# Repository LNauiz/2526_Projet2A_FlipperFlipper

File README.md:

# 2526_Projet2A_Flipper
Notre objectif est de réaliser un Flipper (ou billard électrique). Notre flipper aurait tous les éléments suivants : les batteurs, les bumpers, un lanceur, un compteur de point et des éclairages (réalisés avec des néopixels), tels que montré sur les dessins suivants : 

Afin de marquer des points, le joueur doit soit passer entre les dauphins soit tapper contre les pièces triangulaires ou contre les bumpers.
### Matériel
* Solénoïdes*4 : Heschen Electroaimant solénoïde, HS-1546B, DC24V, 1.5A, course 20 mm, type Push Pull

* Néopixels alimentées à 5 V

* Photodiodes*3

* Détails de la PCB seront donnés dans la partie concernée

### Logiciels utilisés
KiCAD (design PCB), STM32CubeIDE (Software), Onshape (Modélisation 3D)

## Les Bumpers

Le fonctionnement du bumper est le suivant : lorsque la balle arrive contre le bumper, elle boucle un circuit entre un anneau proche du circuit ainsi que le cylindre central ce qui va provoquer l'abattement d'une collerette (nommée "metal flange with studs" sur le schéma) repoussant ainsi la balle.
Pour réaliser cet "abattement" on utilise des **solénoïdes** que nous commençons par tester : 
### _Premier test solénoïde_

Afin d'utiliser ces solénoïdes pour réaliser des bumpers nous avons besoin d'un support (que nous avons dessiné sur Onshape) :

Pour relier la colerette au solénoïde, on utilise des tiges filetés et des écrous nylstop ainsi qu'une pièce imprimé en 3d calée dans le solénoïde.

Afin de détecter si la balle a touché le bumper, nous avons entouré la base et le mât du bumper de scotch cuivré. La balle, en contact avec les deux morceaux de scotch, ferme le cicuit connecté à un GPIO pin de la STM, ce qui permet de commander le solénoïde du bumper.

## Les Batteurs
Les batteurs sont au nombre de 2 et seront contrôlés par des boutons poussoirs qui activeront d'autres solénoïdes. Ainsi nous avons du réaliser un dispositif afin de pouvoir tranformer la translation produite par le solénoïde en rotation de 60° pour les batteurs. Par Onshape, on modélise les pièces suivantes : 

Il est nécessaire d'ajouter des écrous nylstops à l'intérieur des pièces pour ne pas que ces derniers se dévissent.\
Malgré cela, on a remarqué que les écrous nylstops avaient une certaine marge de mouvement, ce qui désaxe les batteurs au fil du temps.

## Le Lanceur
La première idée afin de réaliser le lanceur est de réaliser un Coilgun dont le principe est le suivant : 
Nous prenons une balle de 25mm de diamètre que nous voulons faire aller à **6 m/s** lors du lancement ainsi le dimmensionnement de notre Coilgun serait le suivant : 

Nous avons fini par nous rabattre sur un simple ressort monté sur une tige filetée.

## Les boutons

Après plusieurs tests, nous avons remarqué que les boutons qui étaient, d'après la datasheet, pour du 5V fonctionnaient en 24V. Afin d'avoir un prototype "fonctionnel", nous avons donc simplement branché les batteurs de cette manière: 24V --- Bouton --- Batteur.\

## Le Compteur
Afin d'afficher le score réalisé par le joueur nous devons réaliser un compteur, on utilisera un afficheur 7 segments.\
Pour ce faire nous utiliserons des Néopixels, le code serait réalisé en langage C.\
Voici le support (réalisé sur Onshape) sur lequel nous voulons coller et souder les néopixels : 

Afin de dissiper la lumière pour ne pas être ébloui par les LED, on peut mettre un difuseur lumineux qui se compose de 1 à 2 couches de PLA.\
Nous avons remarqué que chaque LED doit être séparé par un mur afin de ne pas éclairer les parties des autres (par exemple: le 1 ressemble au 3 sans mur).

## Les Photodiodes
Afin de détecter lorsque la balle passe entre les obstacles ou lorsqu'elle heurte l'obstacle triangulaire du milieu de la table, nous utilisons des photodiodes.
Les premiers tests avec un PCB fait par Monsieur Papazoglou ont été laborieux, on remarque que pour vérifier que ces photodiodes sont bien fonctionnelles nous pouvons lorsqu'elles sont branchées utiliser l'appareil photo de notre téléphone, lorsqu'une lumière violette (le laser) émane de la photodiode, cette dernière est fonctionnelle, si ce n'est pas le cas cela signifie que la photodiode a subi une dégradation irréversible (sûrement du à une alimentation excessive).

## Le PCB
Afin de commander les solénoïdes nous avons réalisé (sur KiCAD) et soudé un premier PCB que voici : 

Lors des soudures nous avons rencontré plusieurs problèmes tels que des empreintes erronées (une résistance R et un condensateur sous-estimés en taille et une patte manquante sur les MOSFETs)
Lors des tests, le Buck de ce premier PCB est fortement monté en température. Nous sommes donc passé au montage suivant (PCB corrigé par Monsieur Papazoglou) :

Lors des test, le Buck de ce PCB est également monté en température. Nous pensons que le problème viendrait d'un court-circuit créé lors de la soudure Pour poursuivre notre projet nous pensons donc changer le buck qui nous cause problème quel que soit le montage par le même type de régulateur à 3 pin que ce celui qui transforme le 24V en 12V. Nous avons construit le PCB avec la possibilité de séparer la partie puissance et la partie commande. Nous avons donc prévu de tester cette dernière lors des prochaines semaines et de commencer à concevoir le PCB final qui commandera l'ensemble du système.

Le PCB final a été réalisé

## Software

Voici le schéma fonctionnel de notre système.

Il nous faut donc jeter un coup d'oeil aux différents capteurs afin de savoir quel information la STM va recevoir. 

## La table de jeux
Afin de réaliser la table de jeux de notre flipper, nous avons décidé de la faire en 2 couches pour y encastrer les différents modules (bumper, batteur...).
Notre première couche est du MDF de 3 mm, gravé afin que nous puissions placer les élèments de la table le mieux possible (rampe de lancement, dauphins...)

Notre deuxième couche est du MDF de 6 mm, des trous d'alignement sont prévus dans les 2 couches pour faciliter la construction

Voici le rendu final de la table, une fois assemblée (il faudrait coller les 2 couches de table pour avoir un meilleur rendu)

## Le Châssis
Afin d'avoir un support pour notre flipper, nous avons dessiné sur Onshape un châssis en prenant en compte la pente réglementaire pour un Flipper classique qui est de **6,5 °**.

Le châssis comporte une ouverture afin d'y brancher l'alimentation ainsi que des aérations permettant la ventilation de notre système.
Après avoir réalisé ceci nous sommes entrain de faire la table de jeux qui sera réalisé en 2 couches (afin de pouvoir varier les épaisseurs et de pouvoir y emboîter les supports pour bumper ou batteur)

# Licence
Licence : MIT

Auteurs : Julie Deissard--Decot, Léonard Navizet, Maxime Beltoise, Johann Mansard

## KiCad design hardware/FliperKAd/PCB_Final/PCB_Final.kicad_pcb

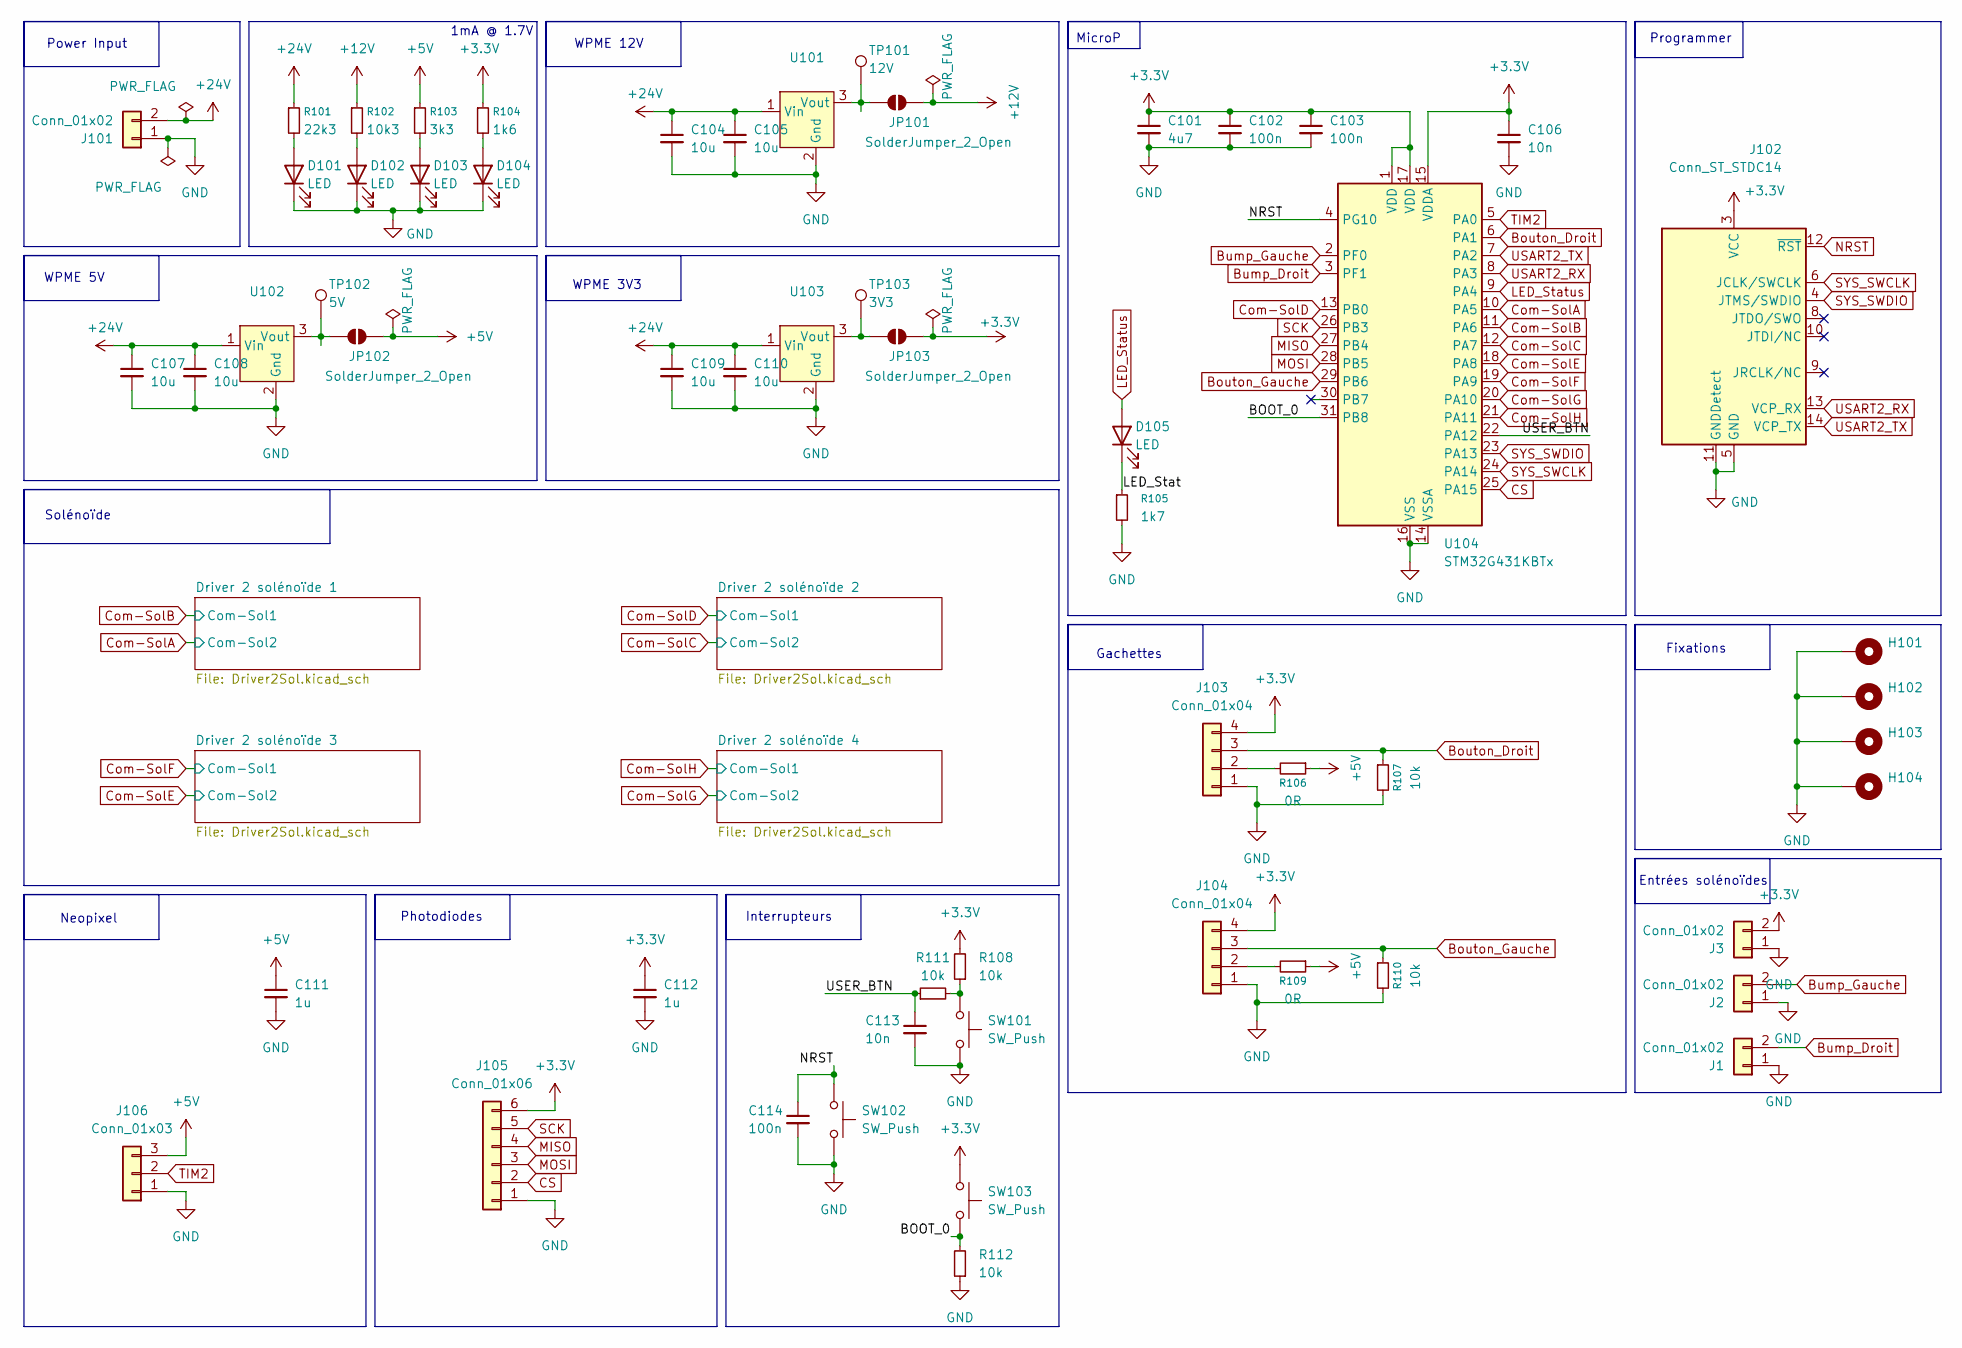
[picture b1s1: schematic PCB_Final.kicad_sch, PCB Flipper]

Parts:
C101: 4u7; C_0603_1608Metric
C102, C103, C114: 100n; C_0402_1005Metric
C104, C105, C107, C108, C109, C110: 10u; C_1206_3216Metric
C106, C113: 10n; C_0402_1005Metric
C111, C112: 1u; C_0603_1608Metric
D101: LED; LED_0603_1608Metric; MPN 150060RS55040
D102, D103, D104, D105: LED; LED_0603_1608Metric
H101, H102, H103, H104: MountingHole_Pad; MountingHole_3.2mm_M3_Pad_Via
J1, J2, J3: Conn_01x02; JST_PH_B2B-PH-K_1x02_P2.00mm_Vertical
J101: Conn_01x02; AMASS_XT30U-F_1x02_P5.0mm_Vertical
J102: Conn_ST_STDC14; PinHeader_2x07_P1.27mm_Vertical_SMD
J103, J104: Conn_01x04; JST_PH_B4B-PH-K_1x04_P2.00mm_Vertical
J105: Conn_01x06; JST_PH_B6B-PH-K_1x06_P2.00mm_Vertical
J106: Conn_01x03; JST_PH_B3B-PH-K_1x03_P2.00mm_Vertical
JP101, JP102, JP103: SolderJumper_2_Open; SolderJumper-2_P1.3mm_Open_TrianglePad1.0x1.5mm
R101: 22k3; R_0402_1005Metric
R102: 10k3; R_0402_1005Metric
R103: 3k3; R_0402_1005Metric
R104: 1k6; R_0402_1005Metric
R105: 1k7; R_0402_1005Metric
R106, R109: 0R; R_0402_1005Metric
R107, R108, R110, R111, R112: 10k; R_0402_1005Metric
SW101, SW102, SW103: SW_Push; SW_SPST_B3U-3000P; MPN KSS221GLFS
TP101: 12V; TestPoint_Pad_D2.0mm
TP102: 5V; TestPoint_Pad_D2.0mm
TP103: 3V3; TestPoint_Pad_D2.0mm
U101: 173951275; MPN 173951275
U102: 173951275; MPN 173950575
U103: 173951275; MPN 173950375
U104: STM32G431KBTx; LQFP-32_7x7mm_P0.8mm

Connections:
+3.3V: C101.1, C102.1, C103.1, C106.1, C112.1, J3.2, J102.3 (VCC), J103.4, J104.4, J105.6, JP103.2 (B), R104.1, R108.2, SW103.1, U104.1 (VDD), U104.15 (VDDA), U104.17 (VDD)
+5V: C111.1, J106.3, JP102.2 (B), R103.1, R106.1, R109.1
+12V: JP101.2 (B), R102.1; also elsewhere on the board
+24V: C104.1, C105.1, C107.1, C108.1, C109.1, C110.1, J101.2, R101.1, U101.1 (Vin), U102.1 (Vin), U103.1 (Vin); also elsewhere on the board
/BOOT_0: R112.2, SW103.2, U104.31 (PB8)
/LED_Stat: D105.1 (K), R105.1
/USER_BTN: C113.1, R111.1, U104.22 (PA12)
Bouton_Droit: J103.3, R107.1, U104.6 (PA1)
Bouton_Gauche: J104.3, R110.1, U104.29 (PB6)
Bump_Droit: J1.2, U104.3 (PF1)
Bump_Gauche: J2.2, U104.2 (PF0)
CS: J105.2, U104.25 (PA15)
Com-SolA: U104.10 (PA5); also elsewhere on the board
Com-SolB: U104.11 (PA6); also elsewhere on the board
Com-SolC: U104.12 (PA7); also elsewhere on the board
Com-SolD: U104.13 (PB0); also elsewhere on the board
Com-SolE: U104.18 (PA8); also elsewhere on the board
Com-SolF: U104.19 (PA9); also elsewhere on the board
Com-SolG: U104.20 (PA10); also elsewhere on the board
Com-SolH: U104.21 (PA11); also elsewhere on the board
GND: C101.2, C102.2, C103.2, C104.2, C105.2, C106.2, C107.2, C108.2, C109.2, C110.2, C111.2, C112.2, C113.2, C114.2, D101.1 (K), D102.1 (K), D103.1 (K), D104.1 (K), H101.1, H102.1, H103.1, H104.1, J1.1, J2.1, J3.1, J101.1, J102.5 (GND), J102.7 (GND), J102.11 (GNDDetect), J103.1, J104.1, J105.1, J106.1, R105.2, R107.2, R110.2, R112.1, SW101.2, SW102.2, U101.2 (Gnd), U102.2 (Gnd), U103.2 (Gnd), U104.14 (VSSA), U104.16 (VSS), U104.32 (VSS); also elsewhere on the board
LED_Status: D105.2 (A), U104.9 (PA4)
MISO: J105.4, U104.27 (PB4)
MOSI: J105.3, U104.28 (PB5)
NRST: C114.1, J102.12 (~RST), SW102.1, U104.4 (PG10)
unnamed: D101.2 (A), R101.2
unnamed: D102.2 (A), R102.2
unnamed: D103.2 (A), R103.2
unnamed: D104.2 (A), R104.2
unnamed: J103.2, R106.2
unnamed: J104.2, R109.2
unnamed: JP101.1 (A), TP101.1, U101.3 (Vout)
unnamed: JP102.1 (A), TP102.1, U102.3 (Vout)
unnamed: JP103.1 (A), TP103.1, U103.3 (Vout)
unnamed: R108.1, R111.2, SW101.1
SCK: J105.5, U104.26 (PB3)
SYS_SWCLK: J102.6 (JCLK/SWCLK), U104.24 (PA14)
SYS_SWDIO: J102.4 (JTMS/SWDIO), U104.23 (PA13)
TIM2: J106.2, U104.5 (PA0)
USART2_RX: J102.13 (VCP_RX), U104.8 (PA3)
USART2_TX: J102.14 (VCP_TX), U104.7 (PA2)

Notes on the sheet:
Entrées solénoïdes
Interrupteurs
1mA @ 1.7V
Neopixel
Fixations
MicroP
Solénoïde
WPME 12V
Programmer
WPME 5V
Power Input
WPME 3V3
Gachettes
Photodiodes

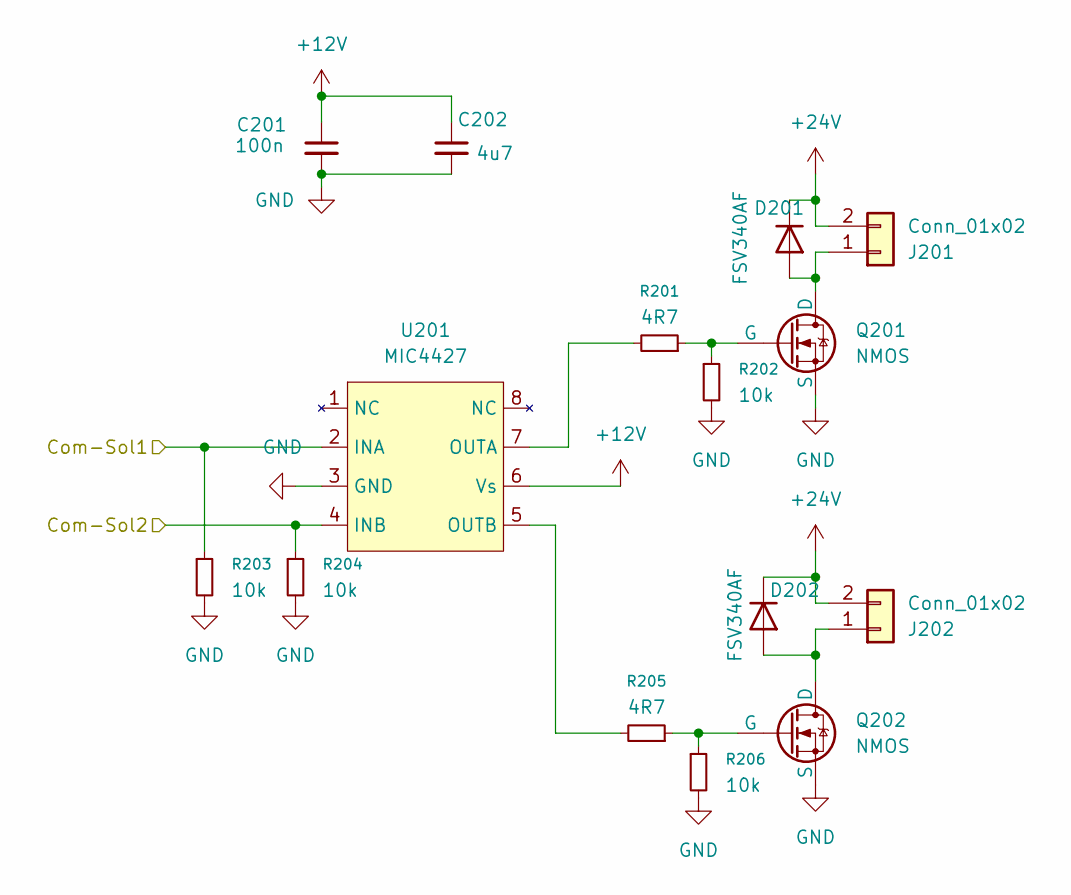
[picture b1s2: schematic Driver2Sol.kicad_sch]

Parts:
C201: 100n; C_0402_1005Metric
C202: 4u7; C_0603_1608Metric
D201, D202: FSV340AF; D_SMA
J201, J202: Conn_01x02; JST_PH_B2B-PH-K_1x02_P2.00mm_Vertical
Q201, Q202: NMOS; BUK
R201, R205: 4R7; R_0402_1005Metric
R202, R203, R204, R206: 10k; R_0402_1005Metric
U201: MIC4427; SOIC-8_5.3x6.2mm_P1.27mm; MPN MIC4427

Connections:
+12V: C201.1, C202.1, U201.6 (Vs); also elsewhere on the board
+24V: D201.1 (K), D202.1 (K), J201.2, J202.2; also elsewhere on the board
Com-SolA: R204.1, U201.4 (INB); also elsewhere on the board
Com-SolB: R203.1, U201.2 (INA); also elsewhere on the board
GND: C201.2, C202.2, Q201.3 (S), Q202.3 (S), R202.2, R203.2, R204.2, R206.2, U201.3 (GND); also elsewhere on the board
unnamed: D201.2 (A), J201.1, Q201.1 (D)
unnamed: D202.2 (A), J202.1, Q202.1 (D)
unnamed: Q201.2 (G), R201.1, R202.1
unnamed: Q202.2 (G), R205.1, R206.1
unnamed: R201.2, U201.7 (OUTA)
unnamed: R205.2, U201.5 (OUTB)

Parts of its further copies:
C301, C401, C501: 100n; C_0402_1005Metric
C302, C402, C502: 4u7; C_0603_1608Metric
D301, D302, D401, D402, D501, D502: FSV340AF; D_SMA
J301, J302, J401, J402, J501, J502: Conn_01x02; JST_PH_B2B-PH-K_1x02_P2.00mm_Vertical
Q301, Q302, Q401, Q402, Q501, Q502: NMOS; BUK
R301, R305, R401, R405, R501, R505: 4R7; R_0402_1005Metric
R302, R303, R304, R306, R402, R403, R404, R406, R502, R503, R504, R506: 10k; R_0402_1005Metric
U301, U401, U501: MIC4427; SOIC-8_5.3x6.2mm_P1.27mm; MPN MIC4427

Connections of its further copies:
+12V: C301.1, C302.1, C401.1, C402.1, C501.1, C502.1, U301.6 (Vs), U401.6 (Vs), U501.6 (Vs); also elsewhere on the board
+24V: D301.1 (K), D302.1 (K), D401.1 (K), D402.1 (K), D501.1 (K), D502.1 (K), J301.2, J302.2, J401.2, J402.2, J501.2, J502.2; also elsewhere on the board
Com-SolC: R304.1, U301.4 (INB); also elsewhere on the board
Com-SolD: R303.1, U301.2 (INA); also elsewhere on the board
Com-SolE: R404.1, U401.4 (INB); also elsewhere on the board
Com-SolF: R403.1, U401.2 (INA); also elsewhere on the board
Com-SolG: R504.1, U501.4 (INB); also elsewhere on the board
Com-SolH: R503.1, U501.2 (INA); also elsewhere on the board
GND: C301.2, C302.2, C401.2, C402.2, C501.2, C502.2, Q301.3 (S), Q302.3 (S), Q401.3 (S), Q402.3 (S), Q501.3 (S), Q502.3 (S), R302.2, R303.2, R304.2, R306.2, R402.2, R403.2, R404.2, R406.2, R502.2, R503.2, R504.2, R506.2, U301.3 (GND), U401.3 (GND), U501.3 (GND); also elsewhere on the board
unnamed: D301.2 (A), J301.1, Q301.1 (D)
unnamed: D302.2 (A), J302.1, Q302.1 (D)
unnamed: D401.2 (A), J401.1, Q401.1 (D)
unnamed: D402.2 (A), J402.1, Q402.1 (D)
unnamed: D501.2 (A), J501.1, Q501.1 (D)
unnamed: D502.2 (A), J502.1, Q502.1 (D)
unnamed: Q301.2 (G), R301.1, R302.1
unnamed: Q302.2 (G), R305.1, R306.1
unnamed: Q401.2 (G), R401.1, R402.1
unnamed: Q402.2 (G), R405.1, R406.1
unnamed: Q501.2 (G), R501.1, R502.1
unnamed: Q502.2 (G), R505.1, R506.1
unnamed: R301.2, U301.7 (OUTA)
unnamed: R305.2, U301.5 (OUTB)
unnamed: R401.2, U401.7 (OUTA)
unnamed: R405.2, U401.5 (OUTB)
unnamed: R501.2, U501.7 (OUTA)
unnamed: R505.2, U501.5 (OUTB)

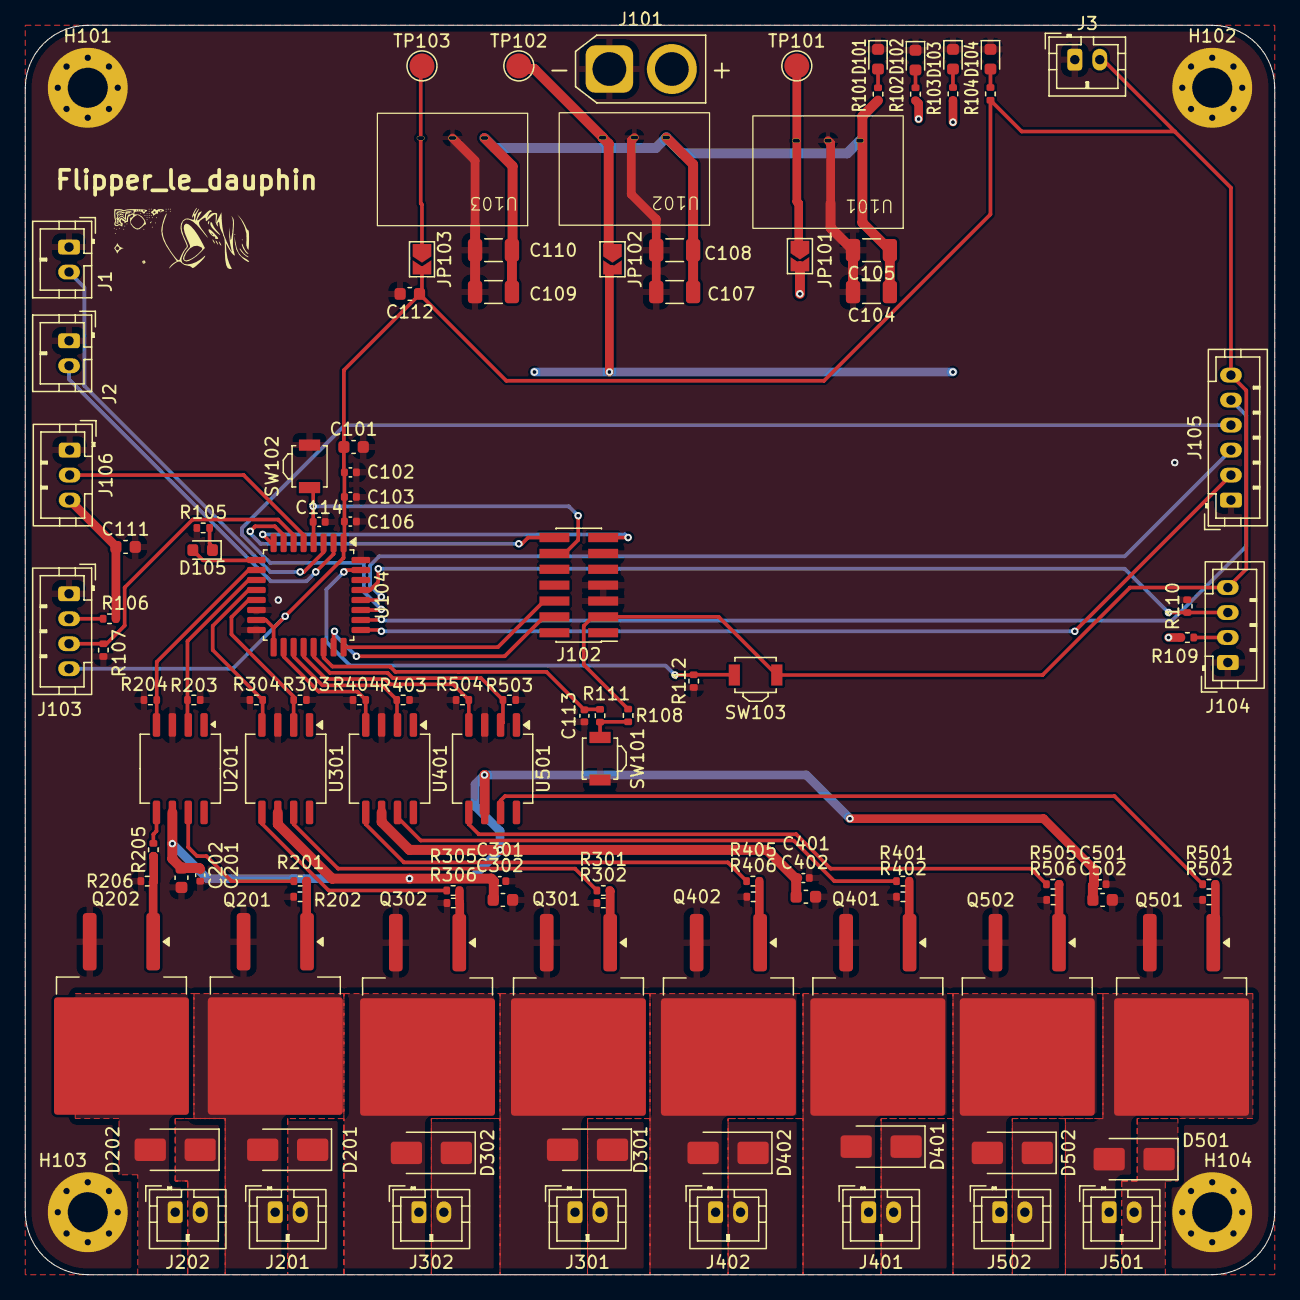
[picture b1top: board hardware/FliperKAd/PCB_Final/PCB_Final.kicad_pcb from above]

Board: 4 copper layers, 100.0 x 100.0 mm, 117 parts (0 on the bottom side), 65 nets.

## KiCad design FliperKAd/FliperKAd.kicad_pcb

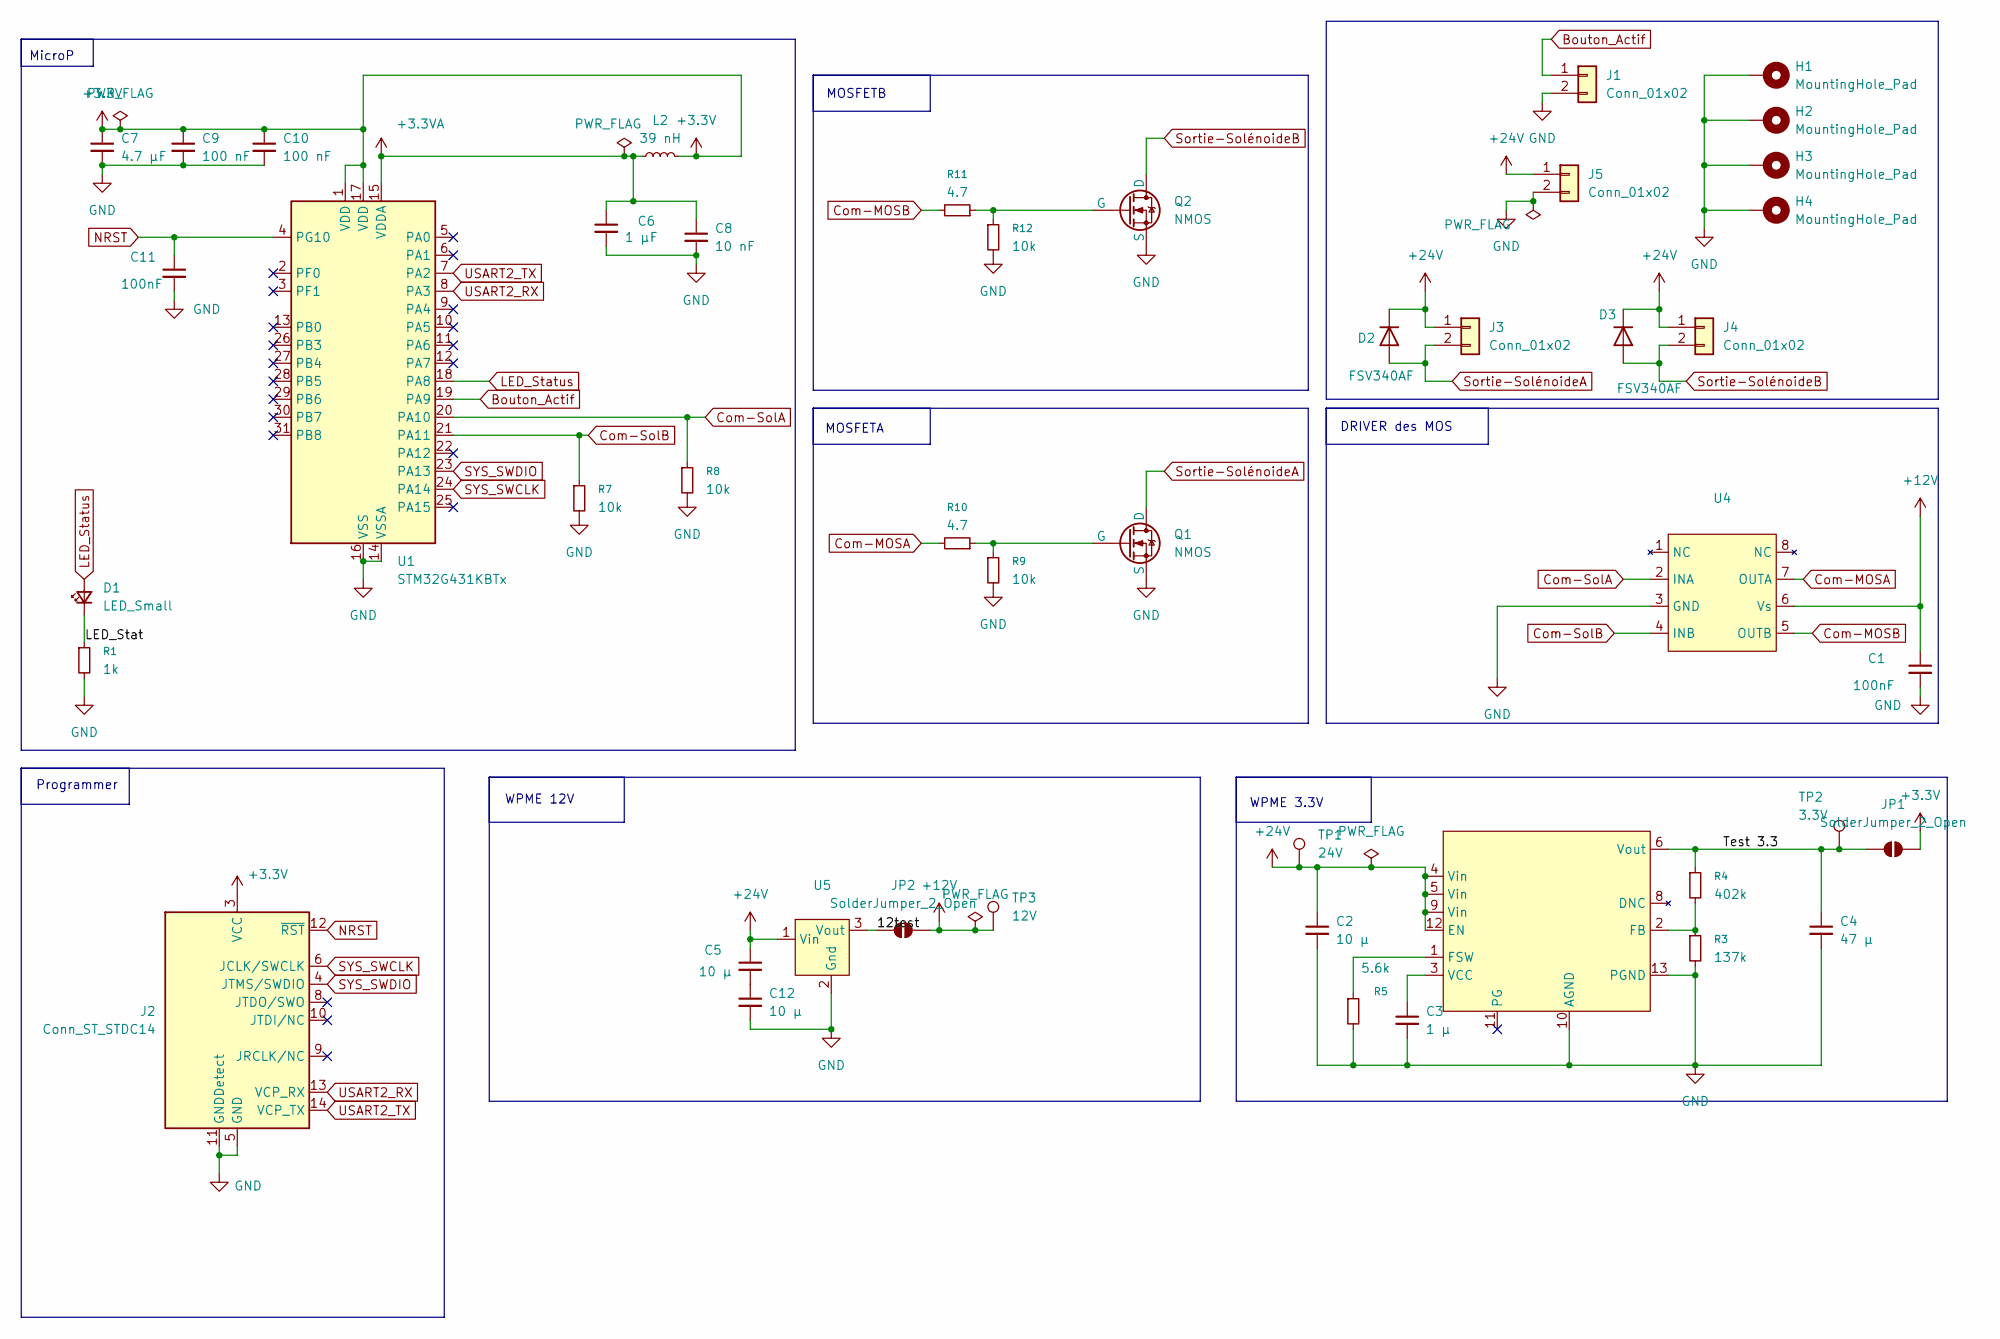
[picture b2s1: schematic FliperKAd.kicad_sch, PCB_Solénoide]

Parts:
C1, C11: 100nF; C_0603_1608Metric
C2, C5, C12: 10 µ; C_0603_1608Metric
C3: 1 µ; C_0603_1608Metric
C4: 47 µ; C_0603_1608Metric
C6: 1 µF; C_0603_1608Metric
C7: 4.7 µF; C_0603_1608Metric
C8: 10 nF; C_0402_1005Metric
C9, C10: 100 nF; C_0402_1005Metric
D1: LED_Small; LED_0603_1608Metric
D2, D3: FSV340AF; D_SMA
H1, H2, H3, H4: MountingHole_Pad; MountingHole_3.2mm_M3_Pad_Via
J1, J3, J4, J5: Conn_01x02; JST_XH_B2B-XH-A_1x02_P2.50mm_Vertical
J2: Conn_ST_STDC14; PinHeader_2x07_P1.27mm_Vertical_SMD
JP1, JP2: SolderJumper_2_Open; SolderJumper-2_P1.3mm_Open_TrianglePad1.0x1.5mm
L2: 39 nH; L_0603_1608Metric
Q1, Q2: NMOS; TO-263-3_TabPin4
R1: 1k; R_0603_1608Metric
R3: 137k; R_0603_1608Metric
R4: 402k; R_0603_1608Metric
R5: 5.6k; R_0603_1608Metric
R7, R8, R9, R12: 10k; R_0603_1608Metric
R10, R11: 4.7; R_0603_1608Metric
TP1: 24V; TestPoint_Pad_D2.0mm
TP2: 3.3V; TestPoint_Pad_D2.0mm
TP3: 12V; TestPoint_Pad_D2.0mm
U1: STM32G431KBTx; LQFP-32_7x7mm_P0.8mm
U3: MCP1640x-xMC; WPME_Magic
U4: MIC4426
U5: 173951275

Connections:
+3.3V: C7.1, C9.1, C10.1, J2.3 (VCC), JP1.2 (B), L2.2, U1.1 (VDD), U1.17 (VDD)
+3.3VA: C6.1, C8.1, L2.1, U1.15 (VDDA)
+12V: C1.1, JP2.2 (B), TP3.1, U4.6 (Vs)
/12test: JP2.1 (A), U5.3 (Vout)
/LED_Stat: D1.1 (K), R1.1
/Test 3.3: C4.1, JP1.1 (A), R4.1, TP2.1, U3.6 (Vout), U3.7 (Vout)
Bouton_Actif: J1.1, U1.19 (PA9)
Com-MOSA: R10.2, U4.7 (OUTA)
Com-MOSB: R11.2, U4.5 (OUTB)
Com-SolA: R8.1, U1.20 (PA10), U4.2 (INA)
Com-SolB: R7.1, U1.21 (PA11), U4.4 (INB)
LED_Status: D1.2 (A), U1.18 (PA8)
NRST: C11.1, J2.12 (~RST), U1.4 (PG10)
unnamed: Q1.2 (G), R9.1, R10.1
unnamed: Q2.2 (G), R11.1, R12.1
unnamed: R3.1, R4.2, U3.2 (FB)
unnamed: R5.1, U3.1 (FSW)
unnamed: C3.1, U3.3 (VCC)
SYS_SWCLK: J2.6 (JCLK/SWCLK), U1.24 (PA14)
SYS_SWDIO: J2.4 (JTMS/SWDIO), U1.23 (PA13)
Sortie-SolénoideA: D2.2 (A), J3.2, Q1.1 (D)
Sortie-SolénoideB: D3.2 (A), J4.2, Q2.1 (D)
USART2_RX: J2.13 (VCP_RX), U1.8 (PA3)
USART2_TX: J2.14 (VCP_TX), U1.7 (PA2)

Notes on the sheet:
MOSFETB
WPME 3.3V
WPME 12V
DRIVER des MOS
MicroP
MOSFETA
Programmer

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
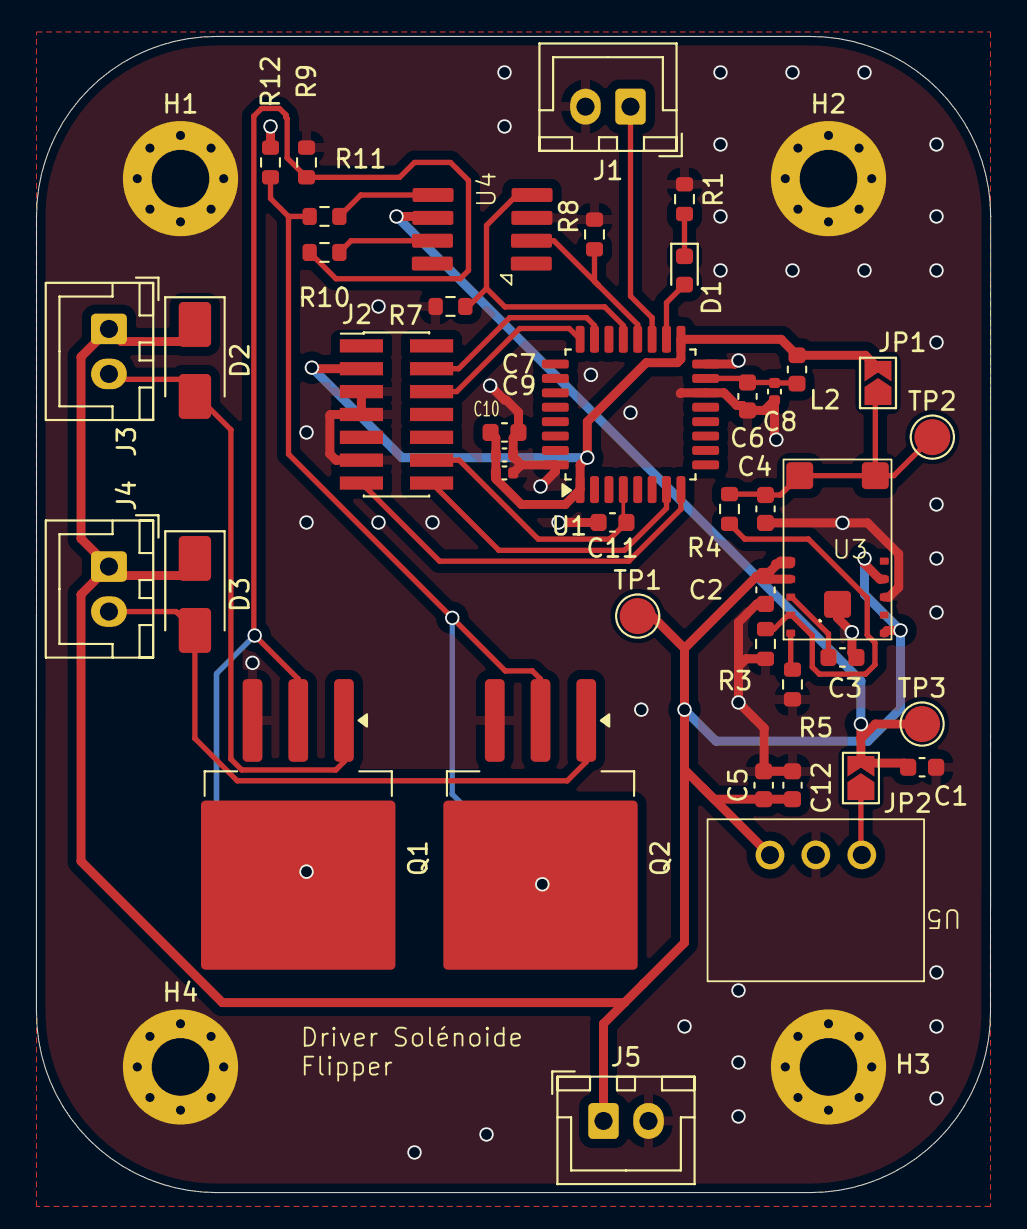
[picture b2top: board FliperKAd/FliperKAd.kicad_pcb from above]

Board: 2 copper layers, 53.0 x 64.2 mm, 46 parts (0 on the bottom side), 26 nets.

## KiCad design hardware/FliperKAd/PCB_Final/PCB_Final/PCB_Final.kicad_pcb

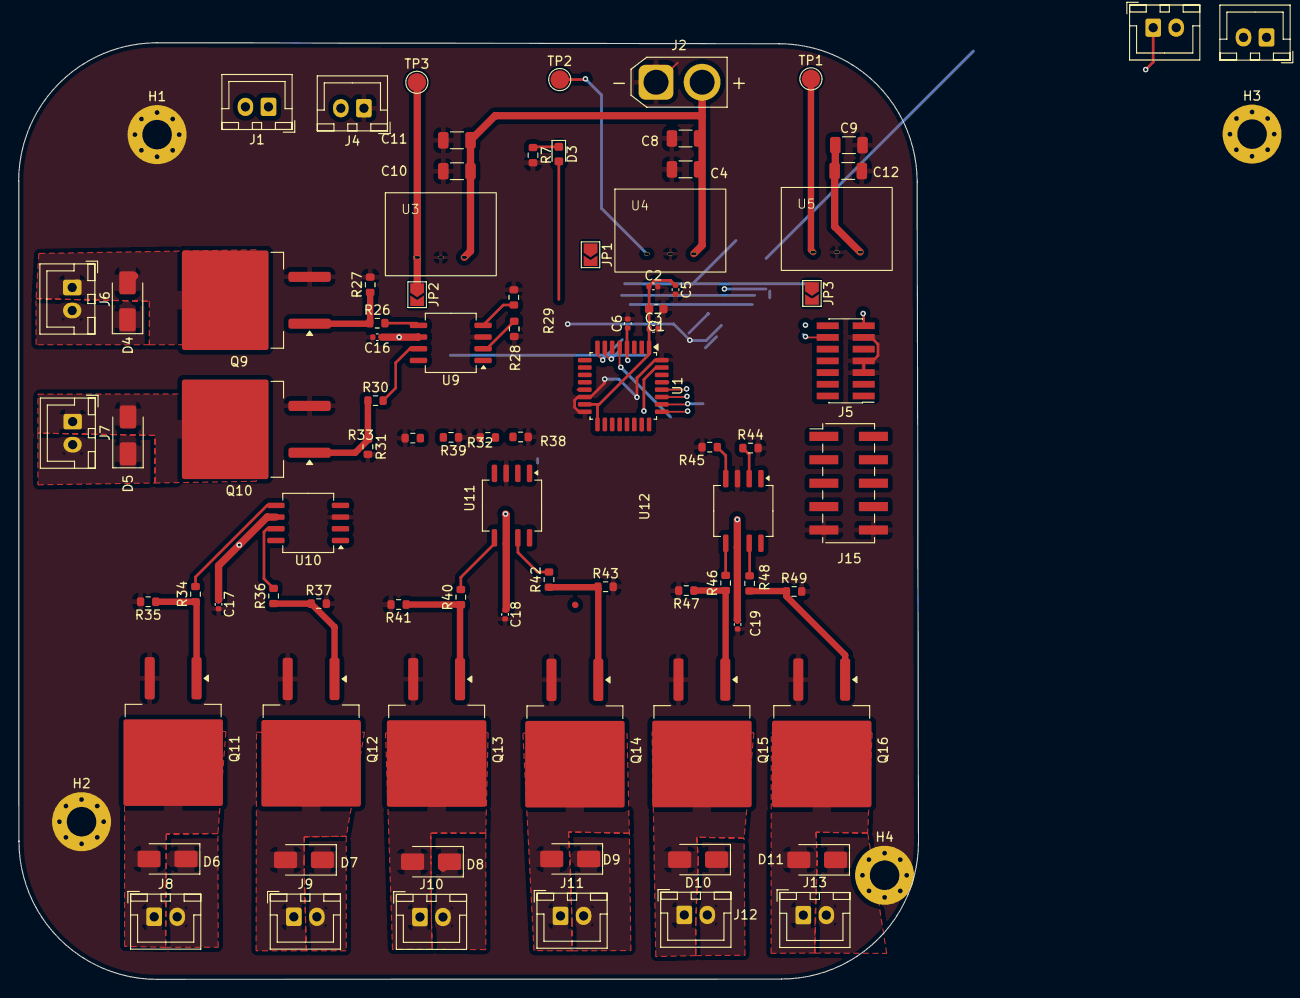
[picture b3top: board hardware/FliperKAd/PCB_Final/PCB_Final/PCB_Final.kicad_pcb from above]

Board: 4 copper layers, 97.6 x 101.6 mm, 90 parts (0 on the bottom side), 54 nets.

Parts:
C1: 4u7; C_0603_1608Metric
C2, C3: 100 nF; C_0402_1005Metric
C4, C8, C9, C10, C11, C12: 10u; C_1206_3216Metric
C5: 10 nF; C_0402_1005Metric
C6, C16, C17, C18, C19: 100nF; C_0402_1005Metric
D3: LED_Small; LED_0603_1608Metric
D4, D5, D6, D7, D8, D9, D10, D11: FSV340AF; D_SMA
H1, H2, H3, H4: MountingHole_Pad; MountingHole_3.2mm_M3_Pad_Via
J1, J3, J4, J6, J7, J8, J9, J10, J11, J12, J13, J14: Conn_01x02; JST_XH_B2B-XH-A_1x02_P2.50mm_Vertical
J2: Conn_01x02; AMASS_XT30U-F_1x02_P5.0mm_Vertical
J5: Conn_ST_STDC14; PinHeader_2x07_P1.27mm_Vertical_SMD
J15: Conn_01x10_MountingPin; 10pins
JP1, JP2, JP3: SolderJumper_2_Open; SolderJumper-2_P1.3mm_Open_TrianglePad1.0x1.5mm
Q9, Q10, Q11, Q12, Q13, Q14, Q15, Q16: NMOS; BUK
R7: 1k; R_0603_1608Metric
R26, R30, R34, R36, R40, R42, R46, R48: 4.7; R_0603_1608Metric
R27, R28, R29, R31, R32, R33, R35, R37, R38, R39, R41, R43, R44, R45, R47, R49: 10k; R_0603_1608Metric
TP1: 5V; TestPoint_Pad_D2.0mm
TP2: 3.3V; TestPoint_Pad_D2.0mm
TP3: 12V; TestPoint_Pad_D2.0mm
U1: STM32G431KBTx; LQFP-32_7x7mm_P0.8mm
U3, U4, U5: 173951275
U9, U10, U11, U12: SOIC-8_5.3x6.2mm_P1.27mm

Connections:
+3.3V: C1.1, C2.1, C3.1, C5.1, J1.2, J5.3 (VCC), J14.2, J15.1, JP1.2 (B), U1.1 (VDD), U1.15 (VDDA), U1.17 (VDD)
+5V: J3.2, J4.2, J15.2, JP3.2 (B)
+12V: C16.1, C17.1, C18.1, C19.1, JP2.2 (B), U9.6 (Vs), U10.6 (Vs), U11.6 (Vs), U12.6 (Vs)
+24V: C4.1, C8.1, C9.1, C10.1, C11.1, C12.1, D4.1 (K), D5.1 (K), D6.1 (K), D7.1 (K), D8.1 (K), D9.1 (K), D10.1 (K), D11.1 (K), J2.2, J6.2, J7.2, J8.2, J9.2, J10.2, J11.2, J12.2, J13.2, U3.1 (Vin), U4.1 (Vin), U5.1 (Vin)
/3.3test: JP1.1 (A), TP2.1, U4.3 (Vout)
/5test: JP3.1 (A), TP1.1, U5.3 (Vout)
/12test: JP2.1 (A), TP3.1, U3.3 (Vout)
/LED_Stat: D3.1 (K), R7.1
Bouton_Droit: J1.1, U1.31 (PB8)
Bouton_Gauche: J14.1, U1.29 (PB6)
CS: J15.7, U1.25 (PA15)
Com-SolA: R29.1, U1.10 (PA5), U9.4 (INB)
Com-SolB: R28.1, U1.11 (PA6), U9.2 (INA)
Com-SolC: R33.1, U1.12 (PA7), U10.4 (INB)
Com-SolD: R32.1, U1.13 (PB0), U10.2 (INA)
Com-SolE: R39.1, U1.18 (PA8), U11.4 (INB)
Com-SolF: R38.1, U1.19 (PA9), U11.2 (INA)
Com-SolG: R45.1, U1.20 (PA10), U12.4 (INB)
Com-SolH: R44.1, U1.21 (PA11), U12.2 (INA)
GND: C1.2, C2.2, C3.2, C4.2, C5.2, C6.2, C8.2, C9.2, C10.2, C11.2, C12.2, C16.2, C17.2, C18.2, C19.2, H1.1, H2.1, H3.1, H4.1, J2.1, J3.1, J4.1, J5.5 (GND), J5.7 (GND), J5.11 (GNDDetect), J15.9, J15.10, Q9.3 (S), Q10.3 (S), Q11.3 (S), Q12.3 (S), Q13.3 (S), Q14.3 (S), Q15.3 (S), Q16.3 (S), R7.2, R27.2, R28.2, R29.2, R31.2, R32.2, R33.2, R35.2, R37.2, R38.2, R39.2, R41.2, R43.2, R44.2, R45.2, R47.2, R49.2, U1.14 (VSSA), U1.16 (VSS), U1.32 (VSS), U3.2 (Gnd), U4.2 (Gnd), U5.2 (Gnd), U9.3 (GND), U10.3 (GND), U11.3 (GND), U12.3 (GND)
LED_Status: D3.2 (A), U1.9 (PA4)
MISO: J15.5, U1.27 (PB4)
MOSI: J15.4, U1.28 (PB5)
NRST: C6.1, J5.12 (~RST), U1.4 (PG10)
unnamed: D4.2 (A), J6.1, Q9.1 (D)
unnamed: D5.2 (A), J7.1, Q10.1 (D)
unnamed: D6.2 (A), J8.1, Q11.1 (D)
unnamed: D7.2 (A), J9.1, Q12.1 (D)
unnamed: D8.2 (A), J10.1, Q13.1 (D)
unnamed: D9.2 (A), J11.1, Q14.1 (D)
unnamed: D10.2 (A), J12.1, Q15.1 (D)
unnamed: D11.2 (A), J13.1, Q16.1 (D)
unnamed: Q9.2 (G), R26.1, R27.1
unnamed: Q10.2 (G), R30.1, R31.1
unnamed: Q11.2 (G), R34.1, R35.1
unnamed: Q12.2 (G), R36.1, R37.1
unnamed: Q13.2 (G), R40.1, R41.1
unnamed: Q14.2 (G), R42.1, R43.1
unnamed: Q15.2 (G), R46.1, R47.1
unnamed: Q16.2 (G), R48.1, R49.1
unnamed: R30.2, U9.7 (OUTA)
unnamed: R26.2, U9.5 (OUTB)
unnamed: R36.2, U10.7 (OUTA)
unnamed: R34.2, U10.5 (OUTB)
unnamed: R42.2, U11.7 (OUTA)
unnamed: R40.2, U11.5 (OUTB)
unnamed: R48.2, U12.7 (OUTA)
unnamed: R46.2, U12.5 (OUTB)
SCK: J15.6, U1.26 (PB3)
SYS_SWCLK: J5.6 (JCLK/SWCLK), U1.24 (PA14)
SYS_SWDIO: J5.4 (JTMS/SWDIO), U1.23 (PA13)
TIM2: J15.8, U1.5 (PA0)
USART2_RX: J5.13 (VCP_RX), U1.8 (PA3)
USART2_TX: J5.14 (VCP_TX), U1.7 (PA2)

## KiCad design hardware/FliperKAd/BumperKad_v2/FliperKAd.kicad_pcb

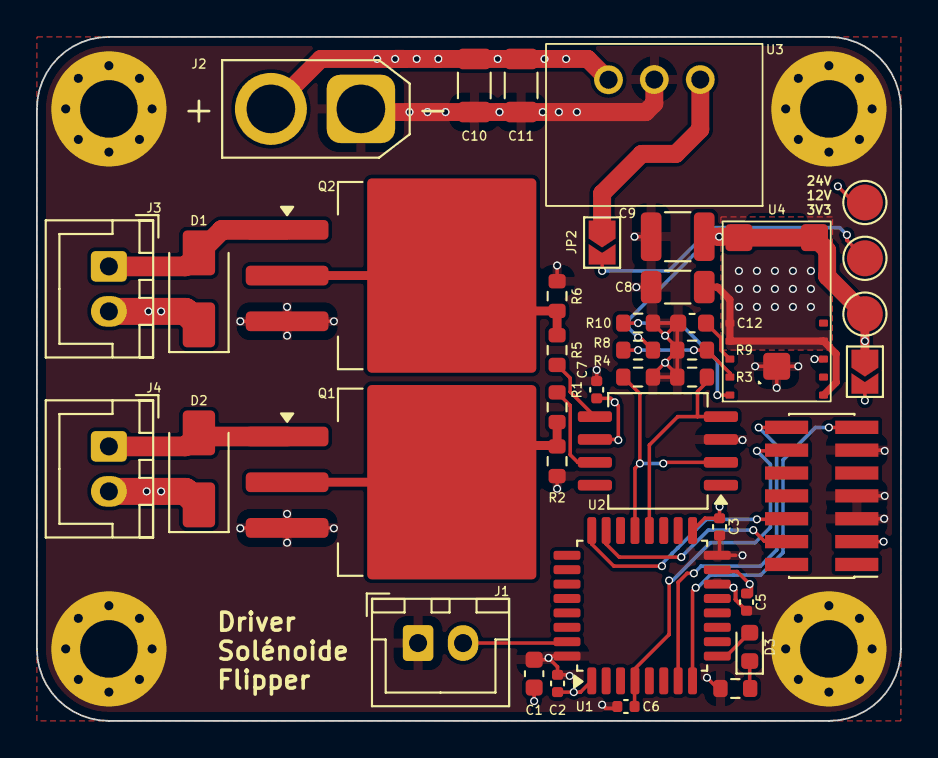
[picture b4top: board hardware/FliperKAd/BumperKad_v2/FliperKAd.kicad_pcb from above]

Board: 4 copper layers, 48.0 x 38.0 mm, 44 parts (0 on the bottom side), 25 nets.

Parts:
C1: 4u7; C_0603_1608Metric
C2, C3: 100 nF; C_0402_1005Metric
C5: 10 nF; C_0402_1005Metric
C6, C7: 100nF; C_0402_1005Metric
C8, C10, C11: 10u; C_1206_3216Metric
C9: 47u; C_1210_3225Metric
C12: 1u; C_0603_1608Metric
D1, D2: FSV340AF; D_SMA
D3: LED_Small; LED_0603_1608Metric
H1, H2, H3, H4: MountingHole_Pad; MountingHole_3.2mm_M3_Pad_Via
J1, J3, J4: Conn_01x02; JST_XH_B2B-XH-A_1x02_P2.50mm_Vertical
J2: Conn_01x02; AMASS_XT30U-F_1x02_P5.0mm_Vertical
J5: Conn_ST_STDC14; PinHeader_2x07_P1.27mm_Vertical_SMD
JP1, JP2: SolderJumper_2_Open; SolderJumper-2_P1.3mm_Open_TrianglePad1.0x1.5mm
Q1, Q2: NMOS; TO-263-3_TabPin2
R1, R5: 4.7; R_0603_1608Metric
R2, R3, R4, R6: 10k; R_0603_1608Metric
R7: 1k; R_0603_1608Metric
R8: 402k; R_0603_1608Metric
R9: 137k; R_0603_1608Metric
R10: 5.6k; R_0603_1608Metric
TP1: 3.3V; TestPoint_Pad_D2.0mm
TP2: 24V; TestPoint_Pad_D2.0mm
TP3: 12V; TestPoint_Pad_D2.0mm
U1: STM32G431KBTx; LQFP-32_7x7mm_P0.8mm
U2: SOIC-8_5.3x6.2mm_P1.27mm
U3: 173951275
U4: MCP1640x-xMC; WPME_Magic

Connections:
+3.3V: C1.1, C2.1, C3.1, C5.1, J5.3 (VCC), JP1.2 (B), U1.1 (VDD), U1.15 (VDDA), U1.17 (VDD)
+12V: C7.1, JP2.2 (B), TP3.1, U2.6 (Vs)
+24V: C8.1, C10.1, C11.1, D1.1 (K), D2.1 (K), J2.2, J3.2, J4.2, TP2.1, U3.1 (Vin), U4.4 (Vin), U4.5 (Vin), U4.9 (Vin), U4.12 (EN)
/12test: JP2.1 (A), U3.3 (Vout)
/LED_Stat: D3.1 (K), R7.1
/Test 3.3: C9.1, JP1.1 (A), R8.1, TP1.1, U4.6 (Vout), U4.7 (Vout)
Bouton_Actif: J1.2, U1.31 (PB8)
Com-MOSA: R5.2, U2.5 (OUTB)
Com-MOSB: R1.2, U2.7 (OUTA)
Com-SolA: R3.1, U1.20 (PA10), U2.4 (INB)
Com-SolB: R4.1, U1.21 (PA11), U2.2 (INA)
GND: C1.2, C2.2, C3.2, C5.2, C6.2, C7.2, C8.2, C9.2, C10.2, C11.2, C12.2, H1.1, H2.1, H3.1, H4.1, J1.1, J2.1, J5.5 (GND), J5.7 (GND), J5.11 (GNDDetect), Q1.3 (S), Q2.3 (S), R2.2, R3.2, R4.2, R6.2, R7.2, R9.2, R10.2, U1.14 (VSSA), U1.16 (VSS), U1.32 (VSS), U2.3 (GND), U3.2 (Gnd), U4.10 (AGND), U4.13 (PGND)
LED_Status: D3.2 (A), U1.9 (PA4)
NRST: C6.1, J5.12 (~RST), U1.4 (PG10)
unnamed: Q1.2 (G), R1.1, R2.1
unnamed: Q2.2 (G), R5.1, R6.1
unnamed: R8.2, R9.1, U4.2 (FB)
unnamed: R10.1, U4.1 (FSW)
unnamed: C12.1, U4.3 (VCC)
SYS_SWCLK: J5.6 (JCLK/SWCLK), U1.24 (PA14)
SYS_SWDIO: J5.4 (JTMS/SWDIO), U1.23 (PA13)
Sortie-SolénoideA: D1.2 (A), J3.1, Q2.1 (D)
Sortie-SolénoideB: D2.2 (A), J4.1, Q1.1 (D)
USART2_RX: J5.13 (VCP_RX), U1.8 (PA3)
USART2_TX: J5.14 (VCP_TX), U1.7 (PA2)
